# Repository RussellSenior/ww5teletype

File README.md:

Exploration of the IBM Wheelwriter 5

This is a project motivated by a desire to create a daisywheel teletype, to give a 
similar experience to that of a Model 33ASR teletype, but with upper and lowercase 
characters. Thanks to Hugh Pyle and his fantastic [Twitch channel](https://www.twitch.tv/33asr) for the 
inspiration.  Thanks also to Chris Gregg and his project:
https://github.com/tofergregg/IBM-Wheelwriter-Hack and to this very similar project 
by Stephen Casner: https://github.com/IBM-1620/Junior.

The goal is to intercept user input from the keyboard and send it to a remote computer
and receive the echoed characters from the remote computer and send the corresponding
commands to the printing mechanism for hardcopy output.

I obtained an IBM Wheelwriter 5 from the Tektronix Surplus Store (open two days a month,
first and third Thursdays, from 2pm to 4pm) on the Beaverton Oregon campus of Tektronix. 
This typewriter came with the parallel port option, which hangs on the back of the case
and interfaces by a 6 (or 7?) pin bus. The cost of the typewriter was $25. I purchased 
two new-in-box ribbon cartridges from the same location for $0.50 each.

Following the lead of Chris Gregg, I began by putting a logic analyzer on the "bus" pin
between the keyboard controller board near the front of the typewriter and the motor 
control board in the rear of the typewriter and watching the response to keystrokes.

The keyboard controller board uses an Intel 8031 (romless version of the venerable 8051).
Reading the MCS-51 MICROCONTROLLER FAMILY USER’S MANUAL from Intel, it appears that the 
interboard communication takes place using a UART signaling but with the wrinkle that
both transmit and receive occur on the same wire. It appears that the UART is placed in 
the so-called "mode 2", which uses a 9-bit message, lsb first, where a one in the ninth bit 
indicates a corresponding target device (specified by the normal 8 bits) on the bus should 
listen to the message. Each message is ACK'd with nine bits of zero, presumably by the 
target device. Communication is at 1/64 of the crystal oscillator speed of 12MHz, which 
works out to 187500 baud (the logic analyzer, a Saleae clone using pulseview of the Sigrok
project, estimated the baud rate was 187060, which is very close, within 1/4%).

My original plan was to man-in-the-middle this serial bus wire, intercepting the commands 
coming from the keyboard controller board, decoding them, and sending a corresponding 
ASCII character (or, perhaps, string) to the remote computer over a normal 8N1 like UART,
receiving a ASCII back from the remote computer and injecting the corresponding commands
on the split bus.  However, due to some challenges, this is easier said than done:

Amongst other things, the keyboard has no "Control" key, therefore it becomes necessary
to hijack another key to act on its behalf. The most obvious candidate is the "Code"
key, which sits on the space bar row, to the left of the space bar. The difficulty arises
when you discover that the combination of "Code" and some other keys generates a rather 
complex series of commands, which would need to be decoded. This isn't impossible, but it
seems like a lot of complex work.

A second alternative, one taken by Stephen Casner for the IBM 1620 Junior project, is to 
intercept key presses directly from the FFC cables coming from the keyboard itself, and decode
the matrix. The corresponding ASCII characters can be sent to the remote computer and a fake
keyboard can be presented to the keyboard controller board.  I need to learn more about how
the keyboard matrix works.

One desirable feature is the ability to return to a "local" (vs "line") mode, where normal
typewriter functionality is restored, either through software or perhaps a hardware switch.

Thanks to the able assistance of [Jared Boone](https://github.com/jboone) of [ShareBrained Technology](https://www.sharebrained.com/), of Chronulator and 
PortaPack fame, I was able to obtain dumps of the off-chip ROMs for the keyboard controller 
and printer option boards (there are some other ROMs, but they seem less important).  They
can be found in the rom subdirectory. The motor control ROM would also be interesting, but
they are more obfuscated than even the keyboard controller board.

One oddity found in the disassembled firmware so far, it's not clear where the UART is 
configured in the keyboard controller firmware. I see references to the control register 
SCON in the printer board firmware, but not in the keyboard controller. Setting up the 
9-bit serial mode must require twiddling that register, so wtf?

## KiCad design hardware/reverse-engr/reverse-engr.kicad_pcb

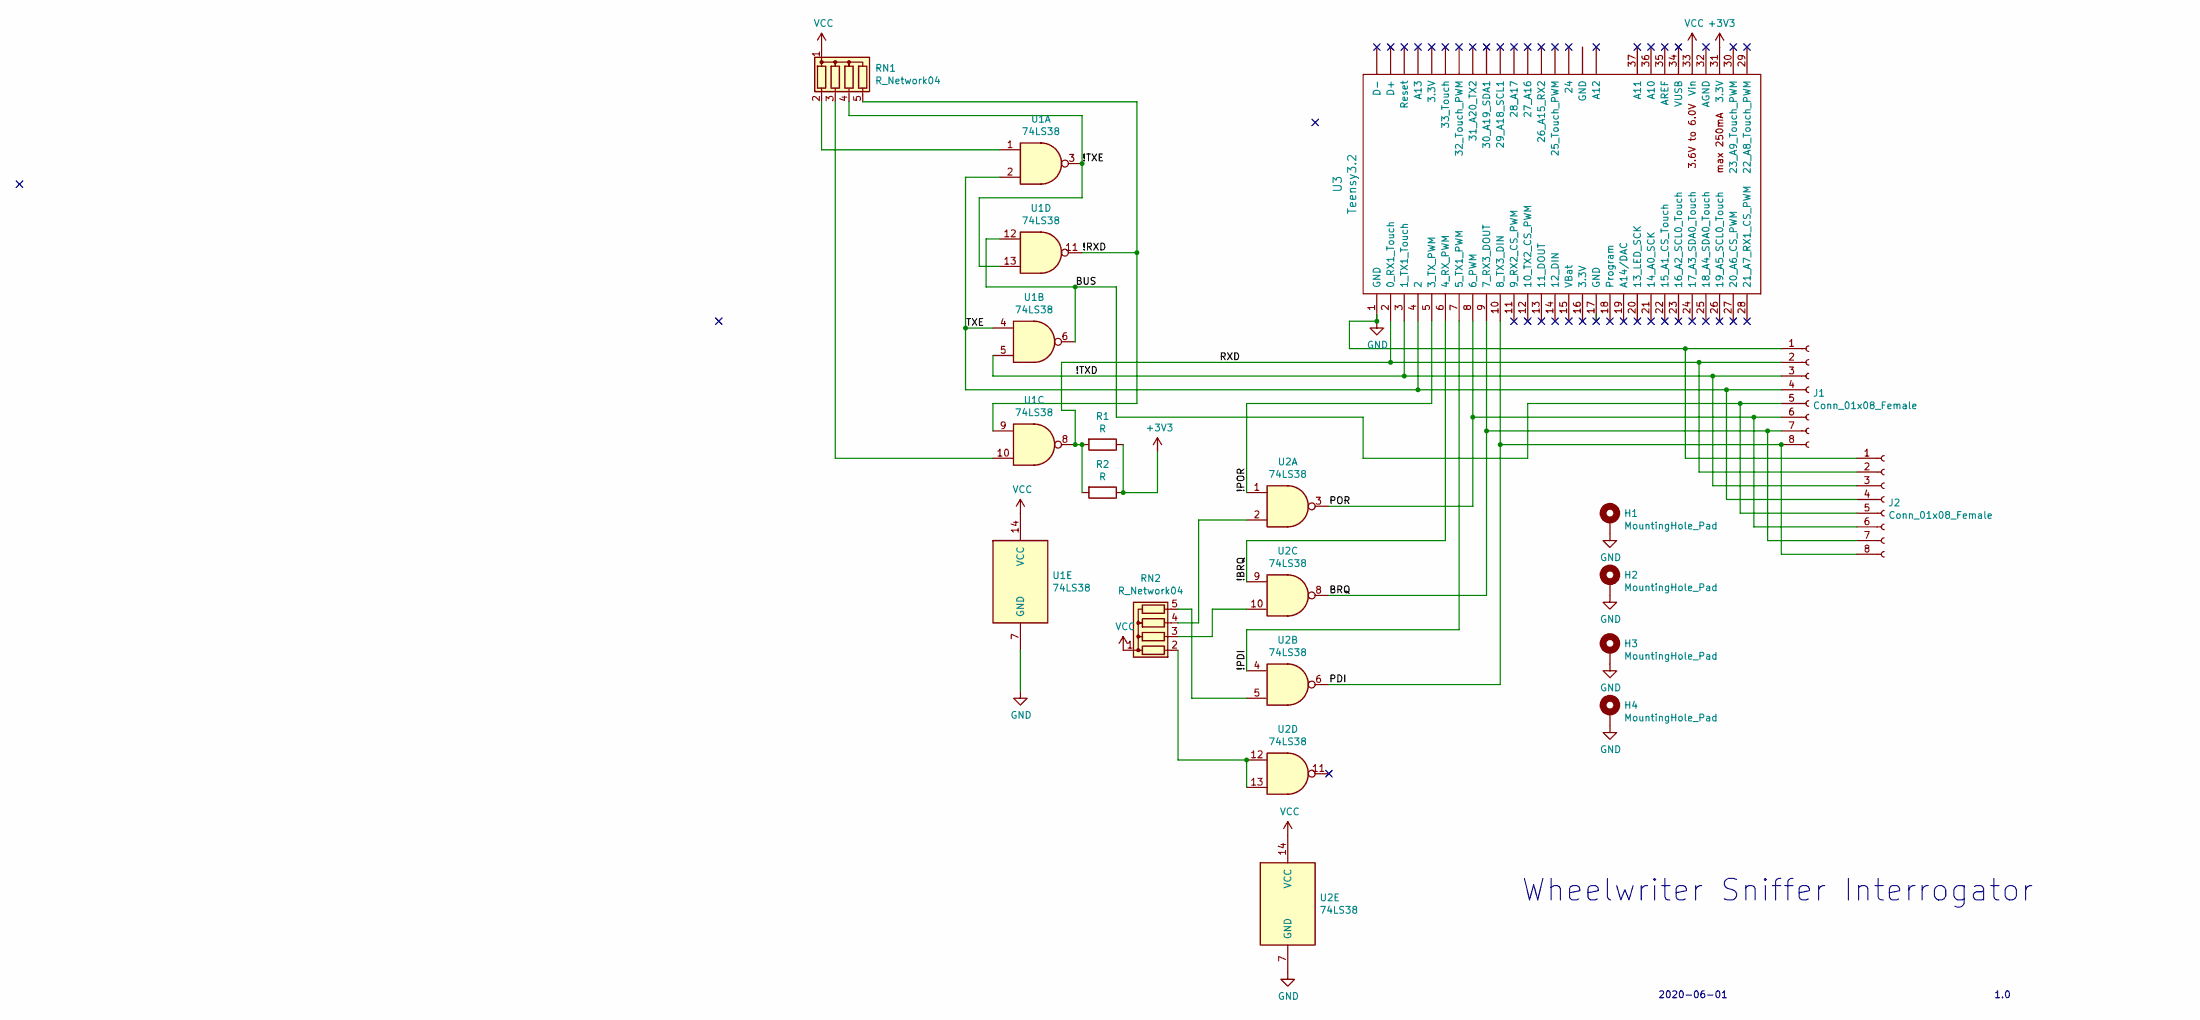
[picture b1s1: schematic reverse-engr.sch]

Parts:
H1, H2, H3, H4: MountingHole_Pad; MountingHole_2.2mm_M2_Pad
J1, J2: Conn_01x08_Female; PinHeader_1x08_P2.54mm_Vertical
R1, R2: R; R_0603_1608Metric
RN1, RN2: R_Network04; R_Array_SIP5
U1, U2: 74LS38; DIP-14_W7.62mm
U3: Teensy3.2; Teensy30_31_32_LC

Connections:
+3V3: R1.1, R2.1, U3.31 (3.3V)
/!BRQ: U2.9, U3.6 (4_RX_PWM)
/!PDI: U2.4, U3.7 (5_TX1_PWM)
/!POR: U2.1, U3.5 (3_TX_PWM)
/!RXD: RN1.5 (R4), U1.9, U1.11
/!TXD: J1.3, J2.3, U1.5, U3.3 (1_TX1_Touch)
/!TXE: RN1.4 (R3), U1.3, U1.13
/BRQ: J1.7, J2.7, U2.8, U3.9 (7_RX3_DOUT)
/BUS: J1.5, J2.5, U1.6, U1.12
/PDI: J1.8, J2.8, U2.6, U3.10 (8_TX3_DIN)
/POR: J1.6, J2.6, U2.3, U3.8 (6_PWM)
/RXD: J1.2, J2.2, R1.2, R2.2, U1.8, U3.2 (0_RX1_Touch)
/TXE: J1.4, J2.4, U1.2, U1.4, U3.4 (2)
GND: H1.1, H2.1, H3.1, H4.1, J1.1, J2.1, U1.7 (GND), U2.7 (GND), U3.1 (GND)
unnamed: RN1.2 (R1), U1.1
unnamed: RN1.3 (R2), U1.10
unnamed: RN2.2 (R1), U2.12, U2.13
unnamed: RN2.3 (R2), U2.10
unnamed: RN2.4 (R3), U2.2
unnamed: RN2.5 (R4), U2.5
VCC: RN1.1 (common), RN2.1 (common), U1.14 (VCC), U2.14 (VCC), U3.33 (Vin)

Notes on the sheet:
Wheelwriter Sniffer Interrogator
1.0
2020-06-01

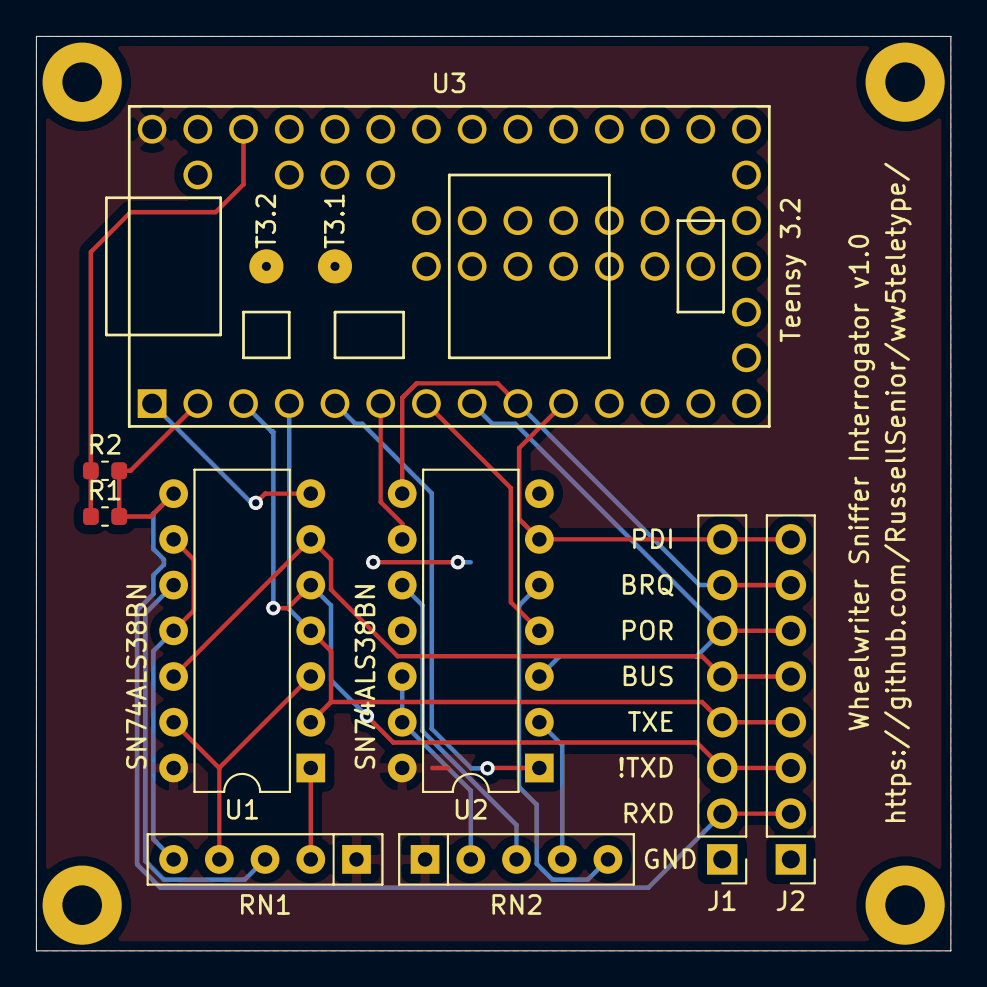
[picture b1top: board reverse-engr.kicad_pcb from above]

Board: 2 copper layers, 50.8 x 50.8 mm, 13 parts (0 on the bottom side), 21 nets.

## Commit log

2019-04-25 first check-in
    includes images of the front and back (flipped) of the keyboard controller
    board.
2019-04-29 add more information, including:
    * ROM dumps from keyboard and parallel printing controller 8031 boards
    * disassembly of those ROM dumps
    * a color coded pcb trace image (still some traces hidden by chips)
2019-04-29 add some exposition about the goals of the project
2019-04-29 add some information about the baud rate
2019-04-29 add a little more detail about keyboard decoding
2019-04-30 clean up typos and add links
2019-04-30 fix markdown links
2019-04-30 linkify the 33asr twitch channel
2020-05-25 clean up README and add some serial protocol deductions
2020-05-25 add some bus traces from pulseview
2020-05-31 observing bus during key presses
2020-05-31 add some discussion about what commands do
2020-05-31 added some more information
2020-06-03 more protocol details
2020-06-03 add kicad sniffer circuit board, currently off getting fabricated by oshpark
2020-06-04 add a description of the mapping for wheel 1353909
    Obtained an ASCII Courier 10 DP PC (reorder number 1353909) and checked
    the character set. The first column is the printwheel address, the
    second column is the printed character, and the third column is the
    ASCII code. This printwheel will let me print a full ASCII character
    set on the wheelwriter.
    The difference between a standard wheelwriter typewheel and this one are
2020-06-09 add some more traces and discussion
2020-06-13 more reverse engineering progress
    discovered the printer option board talks to the function board in terms
    of pseudo key press/releases. the key codes are included in
    doc/printwheel-map-with-option-board-codes.txt. See the bus traffic in
    doc/bus-traffic-chars.txt.
2020-06-14 add some missing shifts
2020-06-14 add some more observed traffic with notes
2020-06-14 refine command explanations
2020-06-16 add ghidra decompiles
2020-06-20 refine the command description a bit
2020-06-27 discovered the paper-load lever switch generates 0x49 key event
